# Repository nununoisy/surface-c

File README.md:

# Surface-C
### By Noah Sweilem

This repository contains the KiCAD and Gerber files for the Surface-C board.

For the BOM and more information, please read [Surface-C-Documentation.pdf](https://github.com/nununoisy/surface-c/tree/master/Surface-C-Documentation.pdf)

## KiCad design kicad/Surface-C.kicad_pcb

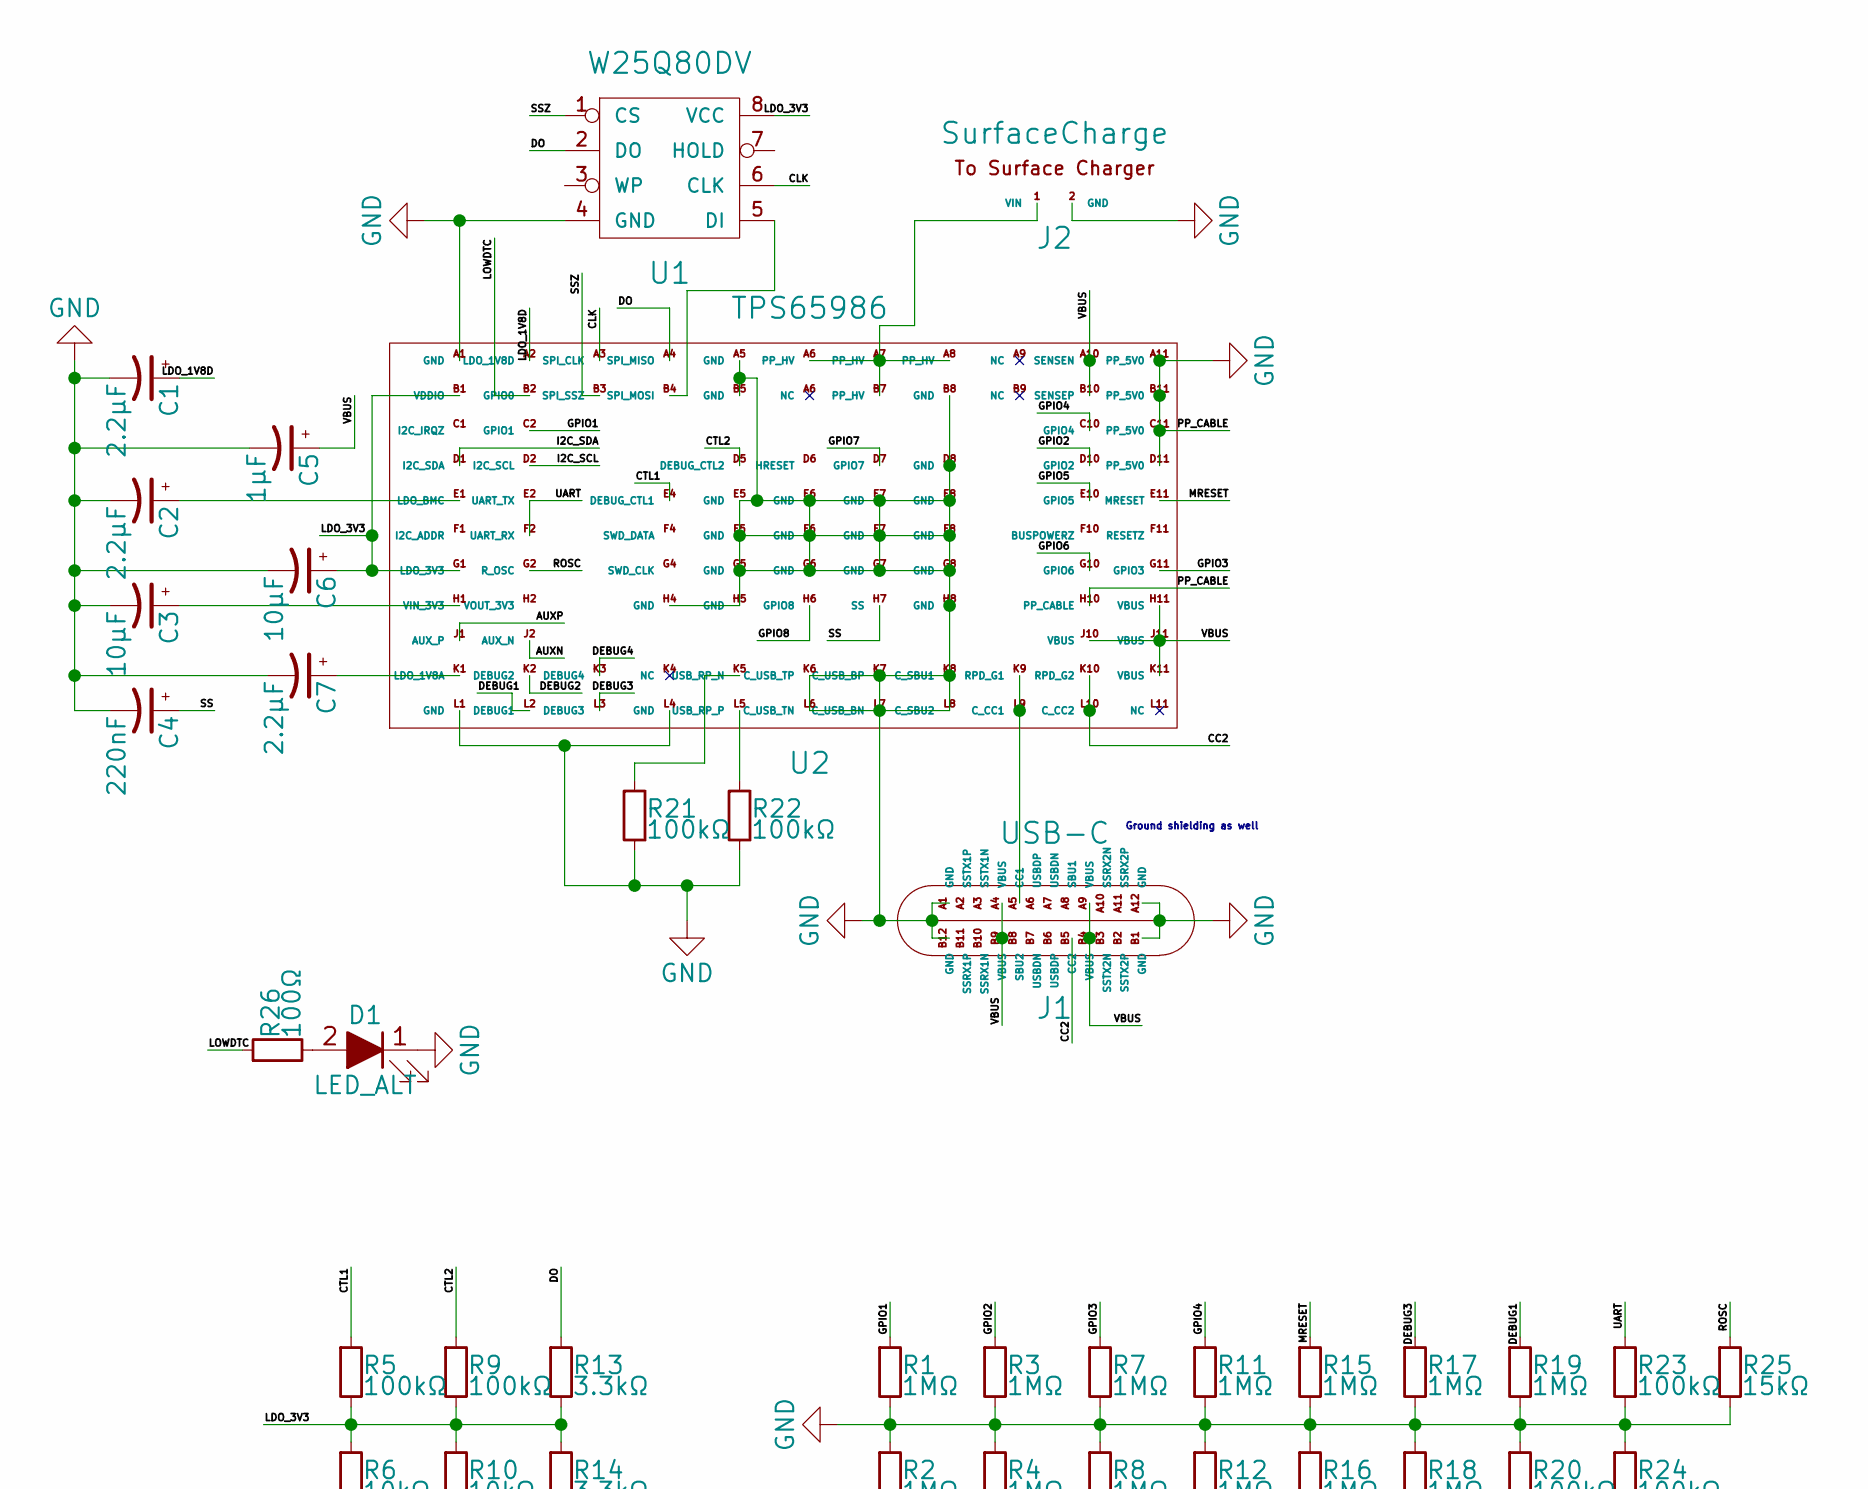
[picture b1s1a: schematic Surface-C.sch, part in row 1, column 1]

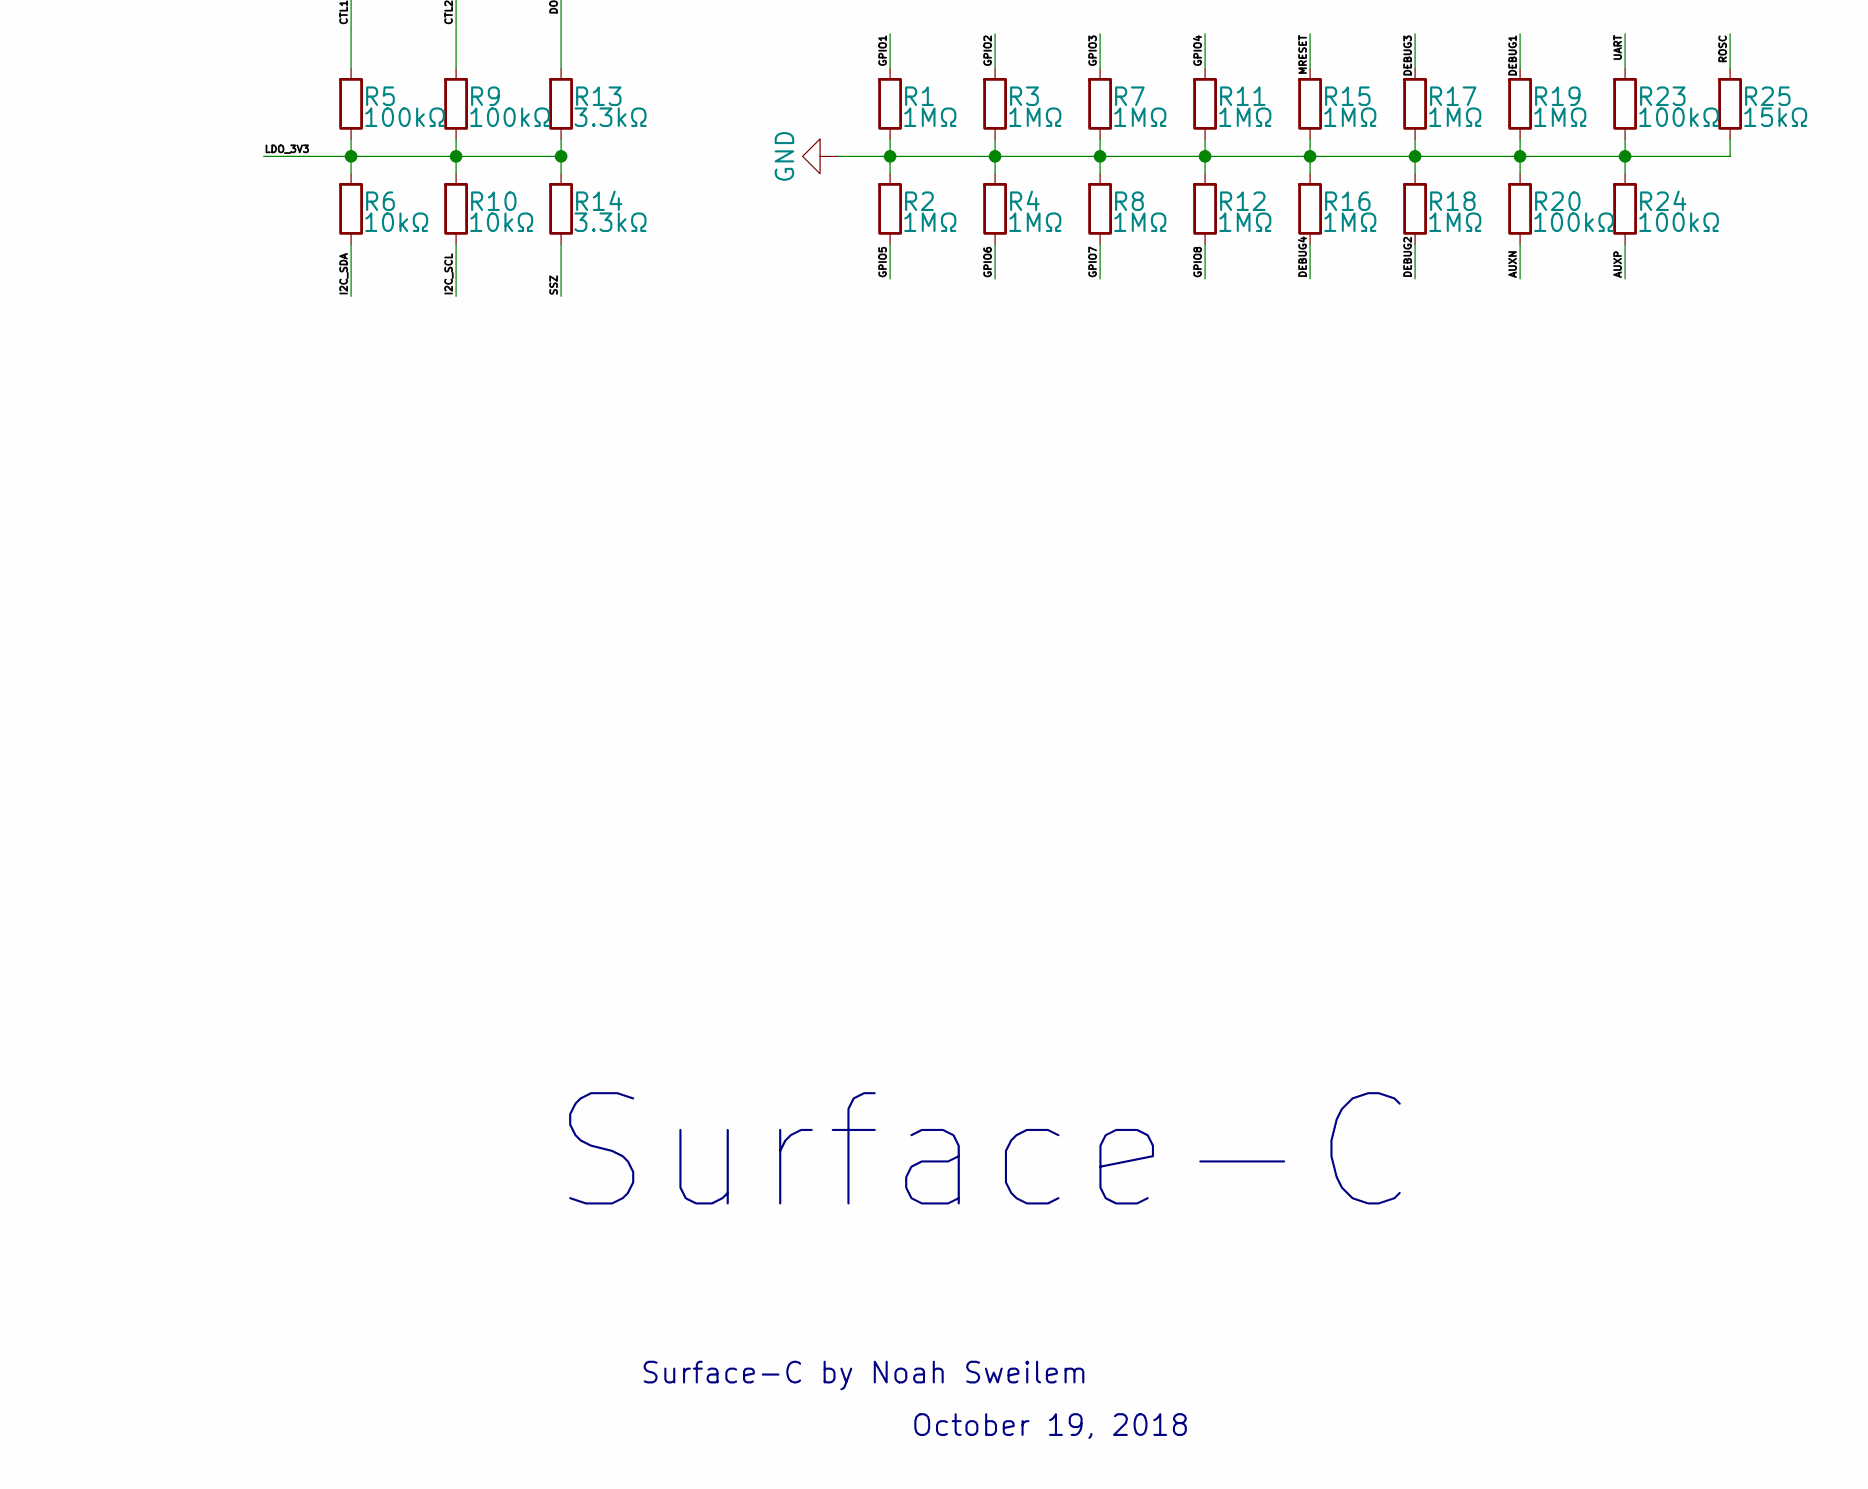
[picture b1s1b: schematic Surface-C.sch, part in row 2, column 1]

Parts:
C1, C2, C7: 2.2μF; c_0402
C3, C6: 10μF; c_0402
C4: 220nF; c_0402
C5: 1μF; c_0402
D1: LED_ALT; LED_1206
J1: USB-C; USB-C_M
J2: SurfaceCharge; WireConnection_0.80mmDrill
R1, R2, R3, R4, R7, R8, R11, R12, R15, R16, R17, R18, R19: 1MΩ; R_0402
R5, R9, R20, R21, R22, R23, R24: 100kΩ; R_0402
R6, R10: 10kΩ; R_0402
R13, R14: 3.3kΩ; R_0402
R25: 15kΩ; R_0402
R26: 100Ω; R_0402
U1: W25Q80DV; SOIC-8_3.9x4.9mm_Pitch1.27mm
U2: TPS65986; ZQZ (S-PBGA-N96)

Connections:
/AUXN: R20.2, U2.J2 (AUX_N)
/AUXP: R24.2, U2.J1 (AUX_P)
/CC2: J1.B5 (CC2), U2.K10 (RPD_G2), U2.L10 (C_CC2)
/CLK: U1.6 (CLK), U2.A3 (SPI_CLK)
/CTL1: R5.1, U2.E4 (DEBUG_CTL1)
/CTL2: R9.1, U2.D5 (DEBUG_CTL2)
/DEBUG1: R19.1, U2.L2 (DEBUG1)
/DEBUG2: R18.2, U2.K2 (DEBUG2)
/DEBUG3: R17.1, U2.L3 (DEBUG3)
/DEBUG4: R16.2, U2.K3 (DEBUG4)
/DO: R13.1, U1.2 (DO), U2.A4 (SPI_MISO)
/GPIO1: R1.1, U2.C2 (GPIO1)
/GPIO2: R3.1, U2.D10 (GPIO2)
/GPIO3: R7.1, U2.G11 (GPIO3)
/GPIO4: R11.1, U2.C10 (GPIO4)
/GPIO5: R2.2, U2.E10 (GPIO5)
/GPIO6: R4.2, U2.G10 (GPIO6)
/GPIO7: R8.2, U2.D7 (GPIO7)
/GPIO8: R12.2, U2.H6 (GPIO8)
/I2C_SCL: R10.2, U2.D2 (I2C_SCL)
/I2C_SDA: R6.2, U2.D1 (I2C_SDA)
/LDO_1V8D: C1.1, U2.A2 (LDO_1V8D)
/LDO_3V3: C6.1, R5.2, R6.1, R9.2, R10.1, R13.2, R14.1, U1.8 (VCC), U2.B1 (VDDIO), U2.G1 (LDO_3V3)
/LOWDTC: R26.1, U2.B2 (GPIO0)
/MRESET: R15.1, U2.E11 (MRESET)
/ROSC: R25.1, U2.G2 (R_OSC)
/SS: C4.1, U2.H7 (SS)
/SSZ: R14.2, U1.1 (CS), U2.B3 (SPI_SSZ)
/UART: R23.1, U2.E2 (UART_TX), U2.F2 (UART_RX)
/VBUS: C5.1, J1.A4 (VBUS), J1.A9 (VBUS), J1.B4 (VBUS), J1.B9 (VBUS), U2.A10 (SENSEN), U2.B10 (SENSEP), U2.H11 (VBUS), U2.J10 (VBUS), U2.J11 (VBUS), U2.K11 (VBUS)
GND: C1.2, C2.2, C3.2, C4.2, C5.2, C6.2, C7.2, D1.1 (K), J1.A1 (GND), J1.A12 (GND), J1.B1 (GND), J1.B12 (GND), J2.2 (GND), R1.2, R2.1, R3.2, R4.1, R7.2, R8.1, R11.2, R12.1, R15.2, R16.1, R17.2, R18.1, R19.2, R20.1, R21.2, R22.2, R23.2, R24.1, R25.2, U1.4 (GND), U2.A1 (GND), U2.A5 (GND), U2.A11 (PP_5V0), U2.B5 (GND), U2.B8 (GND), U2.B11 (PP_5V0), U2.C11 (PP_5V0), U2.D8 (GND), U2.D11 (PP_5V0), U2.E5 (GND), U2.E6 (GND), U2.E7 (GND), U2.E8 (GND), U2.F5 (GND), U2.F6 (GND), U2.F7 (GND), U2.F8 (GND), U2.G5 (GND), U2.G6 (GND), U2.G7 (GND), U2.G8 (GND), U2.H4 (GND), U2.H5 (GND), U2.H8 (GND), U2.H10 (PP_CABLE), U2.K6 (C_USB_TP), U2.K7 (C_USB_BP), U2.K8 (C_SBU1), U2.L1 (GND), U2.L4 (GND), U2.L6 (C_USB_TN), U2.L7 (C_USB_BN), U2.L8 (C_SBU2)
unnamed: C2.1, U2.E1 (LDO_BMC)
unnamed: C3.1, U2.H1 (VIN_3V3)
unnamed: C7.1, U2.K1 (LDO_1V8A)
unnamed: D1.2 (A), R26.2
unnamed: J1.A5 (CC1), U2.K9 (RPD_G1), U2.L9 (C_CC1)
unnamed: R21.1, U2.K5 (USB_RP_N)
unnamed: R22.1, U2.L5 (USB_RP_P)
unnamed: U1.5 (DI), U2.B4 (SPI_MOSI)

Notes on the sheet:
Surface-C
Surface-C by Noah Sweilem
October 19, 2018
Ground shielding as well

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
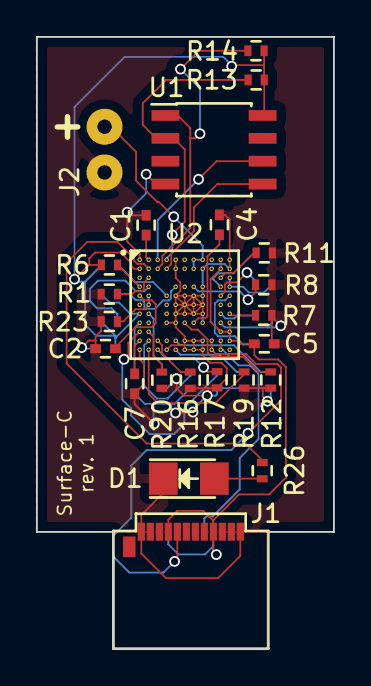
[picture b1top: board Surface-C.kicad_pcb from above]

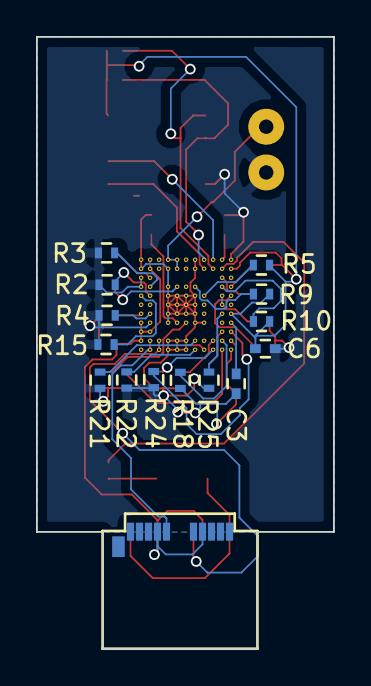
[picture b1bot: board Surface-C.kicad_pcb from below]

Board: 2 copper layers, 16.5 x 34.0 mm, 38 parts (14 on the bottom side), 40 nets.

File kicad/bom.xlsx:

Designator | Value | Package | Populate | MPN
C5 | 1uF | 402 | 1 | GRM155R61C105KA12D
C3,C6 | 10uF | 402 | 2 | GRM155R60G106ME44D
C1,C2,C7 | 2.2uF | 402 | 3 | GRT155C81C225KE13D
C4 | 220nF | 402 | 1 | LLL153C80J224ME14E
D1 |  | 1206 | 1 | LTW-150TK
J1 |  |  | 1 | 1054440001
R13,R14 | 3.3k | 402 | 2 | CRCW04023K30FKEDC
R26 | 100 | 402 | 1 | CRCW0402100RFKEDC
R23,R22,R21,R24,R20,R5,R9 | 100k | 402 | 7 | CRCW0402100KFKEDC
R25 | 15k | 402 | 1 | CRCW040215K0FKEDC
R1,R3,R7,R11,R2,R4,R8,R12,R15,R16,R17,R18,R19 | 1M | 402 | 13 | RCS04021M00FKED
R6,R10 | 10k | 402 | 2 | CRCW040210K0FKEDC
U2 |  | 96-BGA MICROSTAR JUNIOR | 1 | TPS65986
U1 |  | SOIC-8 | 1 | W25Q80DV

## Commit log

2018-10-20 GitHub wants strict formatting I guess
2018-10-20 I forgot my markdown now (*facepalm*)
2018-10-20 Fix space (because they're not allowed). Who wants readable filenames anyway?
2018-10-20 Fix typo
2018-10-23 More documentation about the process
